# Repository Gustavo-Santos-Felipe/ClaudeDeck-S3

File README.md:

# ClaudeDeck S3

A custom 3x3 mechanical macropad powered by the ESP32-S3, featuring a 0.91" OLED display and per-key RGB lighting.

## Project Structure

```text
ClaudeDeck-S3/
├── CAD/
│   ├── BOM.csv
│   ├── README.md
│   └── enclosure/
├── PCB/
│   ├── BOM.csv
│   ├── ClaudeDeck-S3.kicad_pcb
│   ├── ClaudeDeck-S3.kicad_sch
│   ├── README.md
│   └── gerbers/
├── docs/
│   ├── project-journal.md
│   ├── schematic.png
│   ├── pcb_layout.png
│   ├── 3D case top view.jpeg
│   └── bottom view of 3D case.jpeg
└── firmware/
```

## Why and How I Made It

I built the ClaudeDeck S3 because I needed a dedicated, programmable hardware interface to speed up my workflow in CAD software (like Fusion 360) and programming IDEs. I wanted something fully customizable, from the mechanical feel of the switches to the macros executed by the ESP32-S3.

## Features

- **Microcontroller:** ESP32-S3-WROOM-1 with Wi-Fi and Bluetooth capabilities.
- **Switches:** 3x3 matrix (9 keys) compatible with standard Cherry MX mechanical switches.
- **Display:** 0.91" I2C OLED screen for real-time status, menus, and feedback.
- **Lighting:** WS2812B RGB LEDs under each switch.
- **Connectivity:** USB-C.

## Electronics and PCB Design

The schematic and PCB layout were designed in KiCad.

PCB source files, fabrication outputs, and electronics BOM are in [`PCB/`](PCB/README.md).

## Mechanical and Enclosure Design

The enclosure was modeled in Autodesk Fusion 360, including the angled case profile, mounting structure, and print-fit clearances.

**Top View (Ergonomic Wedge):**

**Bottom View (Debossed Logo & Feet Cavities):**

CAD files and enclosure hardware BOM are in [`CAD/`](CAD/README.md).

## Bill of Materials

- **Electronics / PCB BOM:** [`PCB/BOM.csv`](PCB/BOM.csv)

- **Enclosure / 3D Printing BOM:** [`CAD/BOM.csv`](CAD/BOM.csv)
- ## Bill of Materials (BOM)

| Item | Quantity | Unit Price | Total Price | Link |
| :--- | :---: | :---: | :---: | :--- |
| **M3 Heat-Set Inserts** | 1 | $2.00 | $2.00 | [View Item](https://lista.mercadolivre.com.br/inserto-roscado-m3) |
| **M3x6mm Screws** | 1 | $2.00 | $2.00 | [View Item](https://lista.mercadolivre.com.br/parafuso-m3x6) |
| **10mm Silicone Rubber Feet (Bumpons)** | 1 | $3.00 | $3.00 | [View Item](https://lista.mercadolivre.com.br/gota-silicone-adesiva-10mm) |
| **PLA / PETG Filament (1Kg)** | 1 | $15.00 | $15.00 | [View Item](https://www.mercadolivre.com.br/filamento-pla-preto-1kg-voolt3d-175mm-premium-para-imprimir-pecas-3d-impressao-3d-cor-preta-modelagem-miniaturas-enfeites-e-projetos-em-impressoras-3d/p/MLB26212091) |
| **Estimated total shipping** | 1 | $0.00 | $0.00 | - |

## Project Journal

Development history and dated enclosure design entries are in [`docs/project-journal.md`](docs/project-journal.md).

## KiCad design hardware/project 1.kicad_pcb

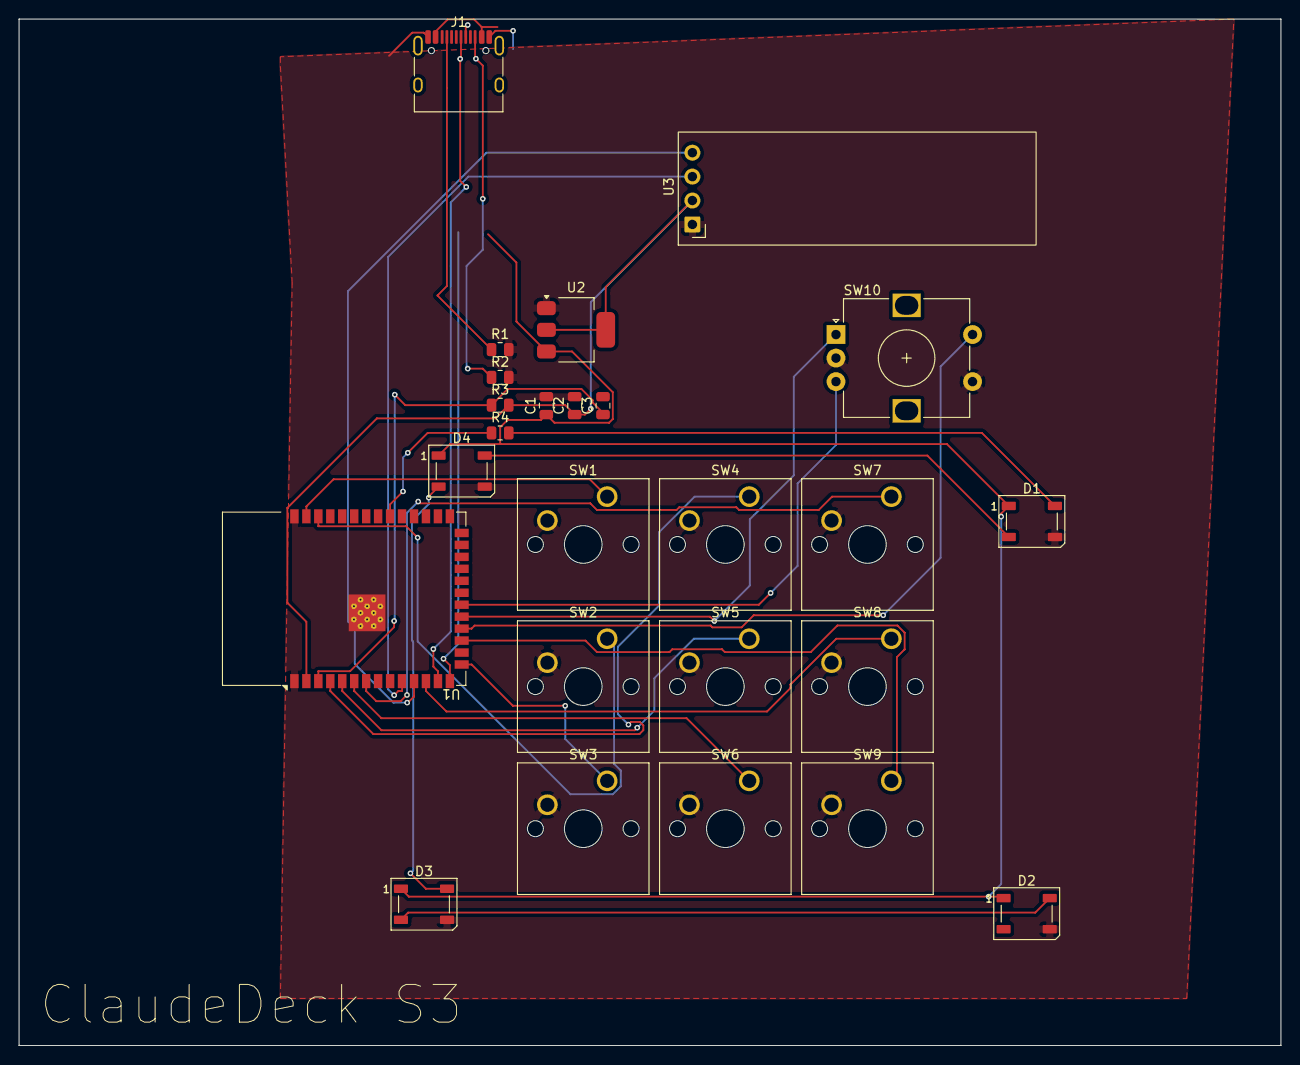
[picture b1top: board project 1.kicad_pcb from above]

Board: 2 copper layers, 134.0 x 109.0 mm, 25 parts (0 on the bottom side), 27 nets.

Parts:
C1, C2: 10µF; C_0805_2012Metric
C3: C; C_0805_2012Metric
D1, D2, D3, D4: WS2812B; LED_WS2812B_PLCC4_5.0x5.0mm_P3.2mm
J1: USB_C_Receptacle_USB2.0_14P; USB_C_Receptacle_HRO_TYPE-C-31-M-12
R1, R2: 5.1kΩ; R_0805_2012Metric
R3: R_US; R_0805_2012Metric
R4: 330Ω; R_0805_2012Metric
SW1, SW2, SW3, SW4, SW5, SW6, SW7, SW8, SW9: SW_Push; SW_Cherry_MX_1.00u_PCB
SW10: RotaryEncoder_Switch; RotaryEncoder_Alps_EC12E-Switch_Vertical_H20mm
U1: ESP32-S3-WROOM-1
U2: AMS1117-3.3; SOT-223-3_TabPin2
U3: ER_OLEDM0.91_1x-I2C

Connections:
/+3V3: C2.1, R3.2, U1.2 (3V3), U2.2 (VO), U3.2 (VCC)
/+5V: C1.1, D1.1 (VDD), D2.1 (VDD), D3.1 (VDD), D4.1 (VDD), J1.A4 (VBUS), J1.A9 (VBUS), J1.B4 (VBUS), J1.B9 (VBUS), U2.3 (VI)
/DOUT1: D1.2 (DOUT), D4.4 (DIN)
/DOUT2: D3.4 (DIN), D4.2 (DOUT)
/DOUT3: D2.4 (DIN), D3.2 (DOUT)
/IO1: SW1.1, U1.39 (IO1)
/IO2: SW2.1, U1.38 (IO2)
/IO3: SW3.1, U1.15 (IO3)
/IO4: SW4.1, U1.4 (IO4)
/IO5: SW5.1, U1.5 (IO5)
/IO6: SW6.1, U1.6 (IO6)
/IO7: SW7.1, U1.7 (IO7)
/IO8: SW8.1, U1.12 (IO8)
/IO9: SW9.1, U1.17 (IO9)
/IO10: SW10.S1, U1.18 (IO10)
/IO11: SW10.A, U1.19 (IO11)
/IO12: SW10.B, U1.20 (IO12)
GND: C1.2, C2.2, C3.2, D1.3 (VSS), D2.3 (VSS), D3.3 (VSS), D4.3 (VSS), J1.A1 (GND), J1.A12 (GND), J1.B1 (GND), J1.B12 (GND), R1.2, R2.2, SW1.2, SW2.2, SW3.2, SW4.2, SW5.2, SW6.2, SW7.2, SW8.2, SW9.2, SW10.C, SW10.S2, U1.1 (GND), U1.40 (GND), U1.41 (GND), U2.1 (GND), U3.1 (GND)
unnamed: D1.4 (DIN), R4.2
unnamed: J1.A5 (CC1), R1.1
unnamed: J1.B5 (CC2), R2.1
unnamed: C3.1, R3.1, U1.3 (EN)
unnamed: U1.10 (IO17), U3.3 (SCL)
unnamed: U1.11 (IO18), U3.4 (SDA)
unnamed: R4.1, U1.32 (IO39)
unnamed: J1.B6 (D+), U1.14 (USB_D+)
unnamed: J1.A7 (D-), U1.13 (USB_D-)
